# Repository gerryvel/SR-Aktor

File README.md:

# SR Actor

## Description
This repository shows how to switch 3 relais (je 4A max with 2x2A contacts) from Chartplotter with CZone Support and also with the website support.
- Switching Relais Aktor

and send it as NNMEA2000 meassage.
- PGN 127501 // Binary Status Report
- PGN 127502 // Binary Switch Control 
- PGN 126208 // Switch Control for B&G
- PGN 130817 
- PGN 65283
- PGN 65284
- PGN 65288
- PGN 65290 CZone  

In addition, the operation of the relays, data and settings can be accessed via the website.

## Based on the work of

The project requires the NMEA2000 and the NMEA2000_esp32 libraries from Timo Lappalainen: https://github.com/ttlappalainen. 

This project is part of [OpenBoatProject](https://open-boat-projects.org/)

## Wiring diagram

## PCB Layout
PCB by Aisler: [Link](https://aisler.net/p/OFGLZJKF)

## Website

## Chartplotter

I use an B&G Vulcan 7 with Czone Support, after import the file:

Configure Czone file with the CZone Configuration tool V 6.29.22

## Fotos

## Changes

- Version 1.3.2 CZone funtion with B&G Vulcan okay
- Version 1.0 Function with Website control, Monitor on NMEA200 okay (PGN127501)

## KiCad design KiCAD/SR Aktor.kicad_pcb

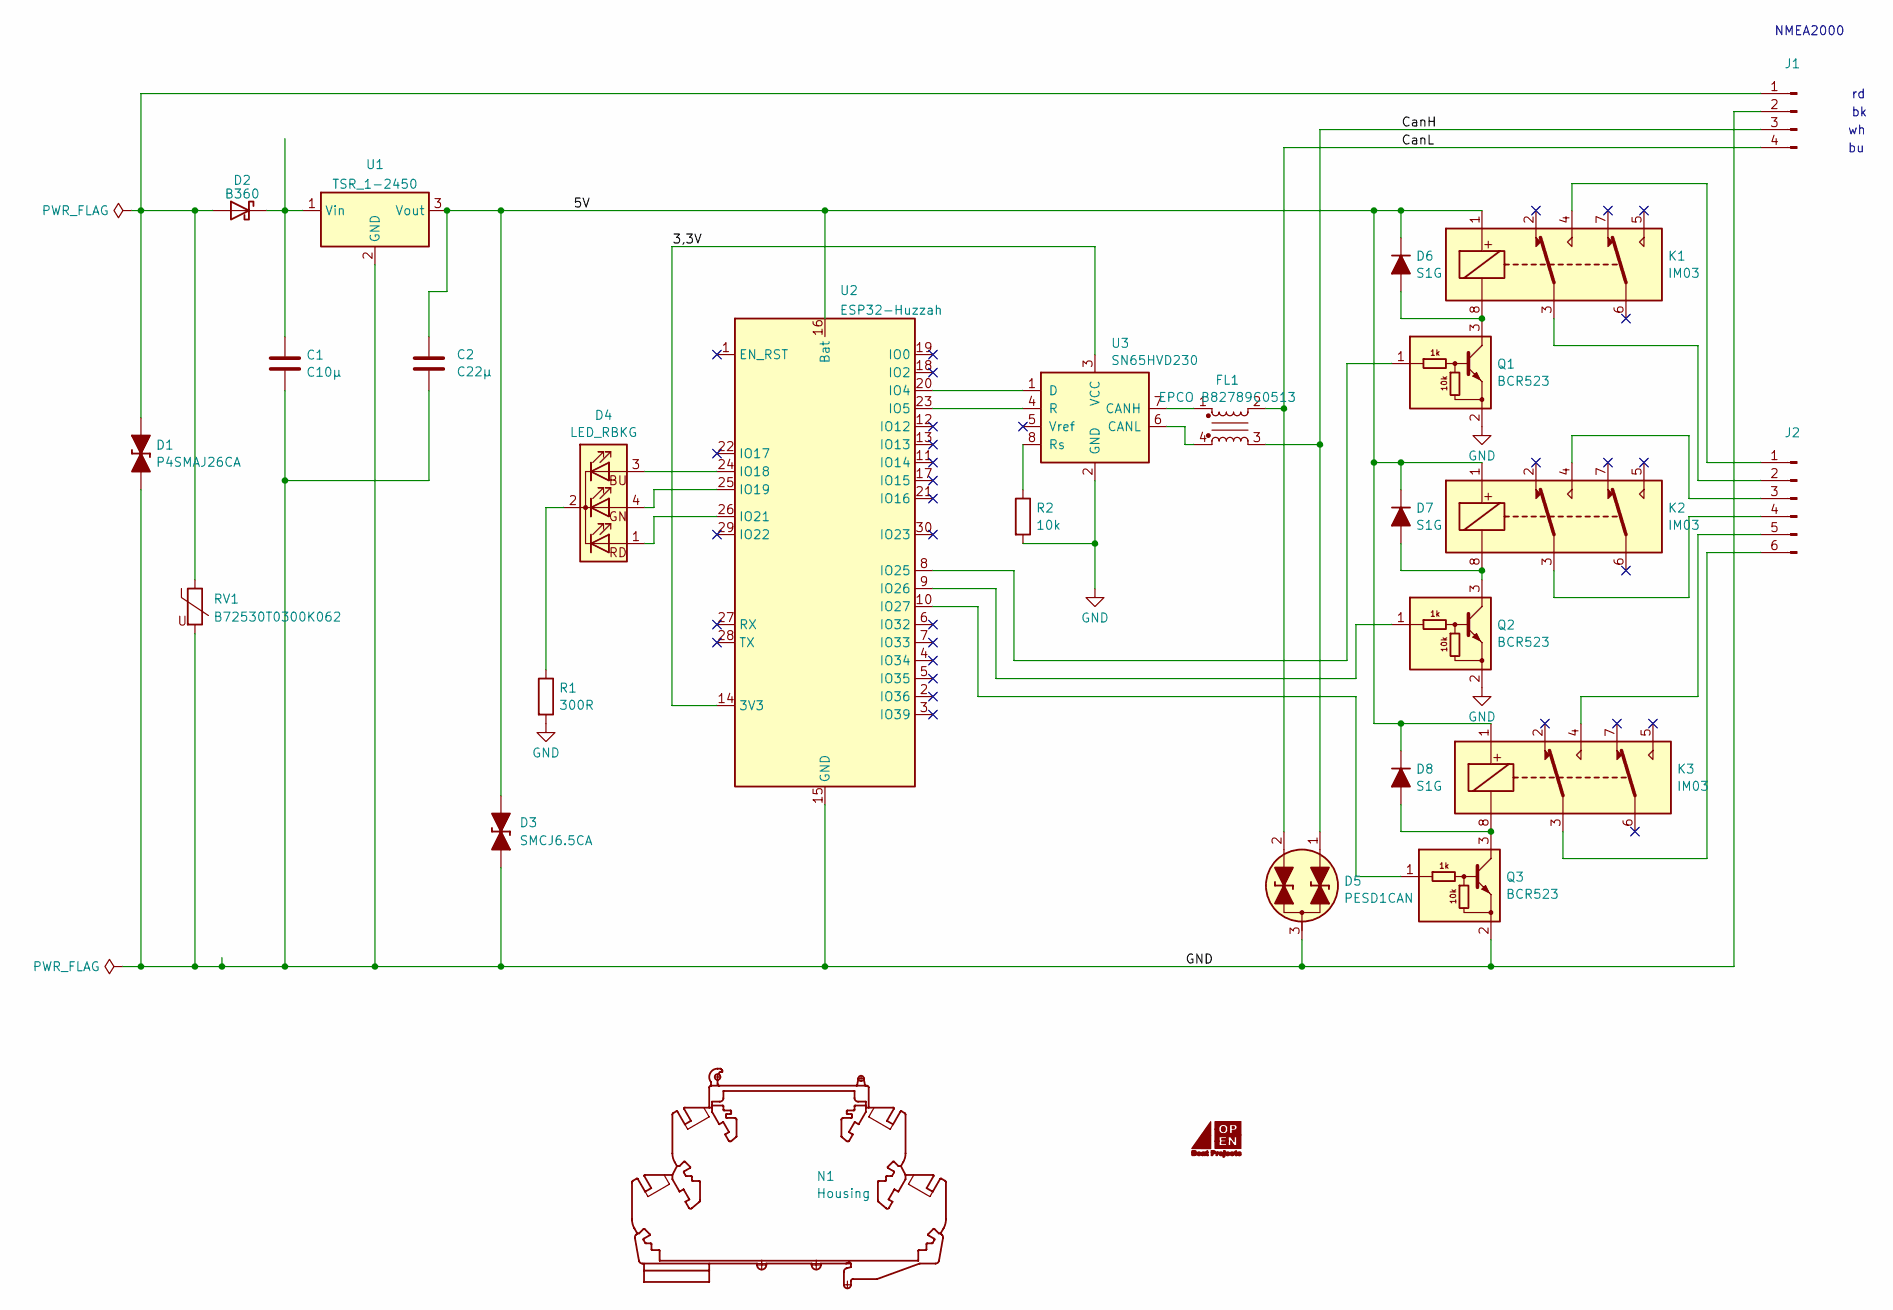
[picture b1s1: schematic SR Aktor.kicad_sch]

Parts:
C1: C10µ; CP_EIA-7343-15_Kemet-W_Pad2.25x2.55mm_HandSolder
C2: C22µ; CP_EIA-7343-15_Kemet-W_Pad2.25x2.55mm_HandSolder
D1: P4SMAJ26CA; D_SMA_TVS
D2: B360; D_SMC
D3: SMCJ6.5CA; D_SMC_TVS
D4: LED_RBKG; PinHeader_1x04_P2.00mm_LED RGB
D5: PESD1CAN; SOT-23
D6, D7, D8: S1G; D_SMA
FL1: EPCO B82789C0513; B82789C0113N002
G1: OpenBoat Logo; Openboatslogo
J1: Conn_01x04_Pin; PinHeader_1x04_P2.54mm_Vertical
J2: Conn_02x03_Pin; PinHeader_2x03_P2.54mm_Vertical
K1, K2, K3: IM03; Relay_DPDT_AXICOM_IMSeries_Pitch5.08mm
N1: Housing; Wago 789-120
Q1, Q2, Q3: BCR523; SOT-23
R1: 300R; R_Axial_DIN0204_L3.6mm_D1.6mm_P7.62mm_Horizontal
R2: 10k; R_Axial_DIN0204_L3.6mm_D1.6mm_P7.62mm_Horizontal
RV1: B72530T0300K062; Fuse_1210_3225Metric_Pad1.42x2.65mm_HandSolder
U1: TSR_1-2450; Converter_DCDC_TRACO_TSR-1_THT
U2: ESP32-Huzzah; Adafruit_ESP32
U3: SN65HVD230; SOIC-8_3.9x4.9mm_P1.27mm

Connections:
/3,3V: U2.14 (3V3), U3.3 (VCC)
/5V: C2.1, D3.1 (K), D6.1 (K), D7.1 (K), D8.1 (K), K1.1, K2.1, K3.1, U1.3 (Vout), U2.16 (Bat)
/CanH: D5.1 (A1), FL1.3, J1.3
/CanL: D5.2 (A2), FL1.2, J1.4
GND: C1.2, C2.2, D1.1 (K), D3.2 (A), D5.3 (Com), J1.2, Q1.2 (E), Q2.2 (E), Q3.2 (E), R1.2, R2.2, RV1.2, U1.2 (GND), U2.15 (GND), U3.2 (GND)
unnamed: D1.2 (A), D2.2 (A), J1.1, RV1.1
unnamed: C1.1, D2.1 (K), U1.1 (Vin)
unnamed: D4.1 (BA), U2.26 (IO21)
unnamed: D4.4 (GA), U2.25 (IO19)
unnamed: D4.2 (K), R1.1
unnamed: D4.3 (R), U2.24 (IO18)
unnamed: D6.2 (A), K1.8, Q1.3 (C)
unnamed: D7.2 (A), K2.8, Q2.3 (C)
unnamed: D8.2 (A), K3.8, Q3.3 (C)
unnamed: J2.1, K1.4
unnamed: J2.2, K1.3
unnamed: J2.3, K2.4
unnamed: J2.4, K2.3
unnamed: J2.5, K3.4
unnamed: J2.6, K3.3
unnamed: Q1.1 (B), U2.8 (IO25)
unnamed: Q2.1 (B), U2.9 (IO26)
unnamed: Q3.1 (B), U2.10 (IO27)
unnamed: U2.20 (IO4), U3.1 (D)
unnamed: U2.23 (IO5), U3.4 (R)
unnamed: FL1.1, U3.7 (CANH)
unnamed: FL1.4, U3.6 (CANL)
unnamed: R2.1, U3.8 (Rs)

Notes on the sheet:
NMEA2000

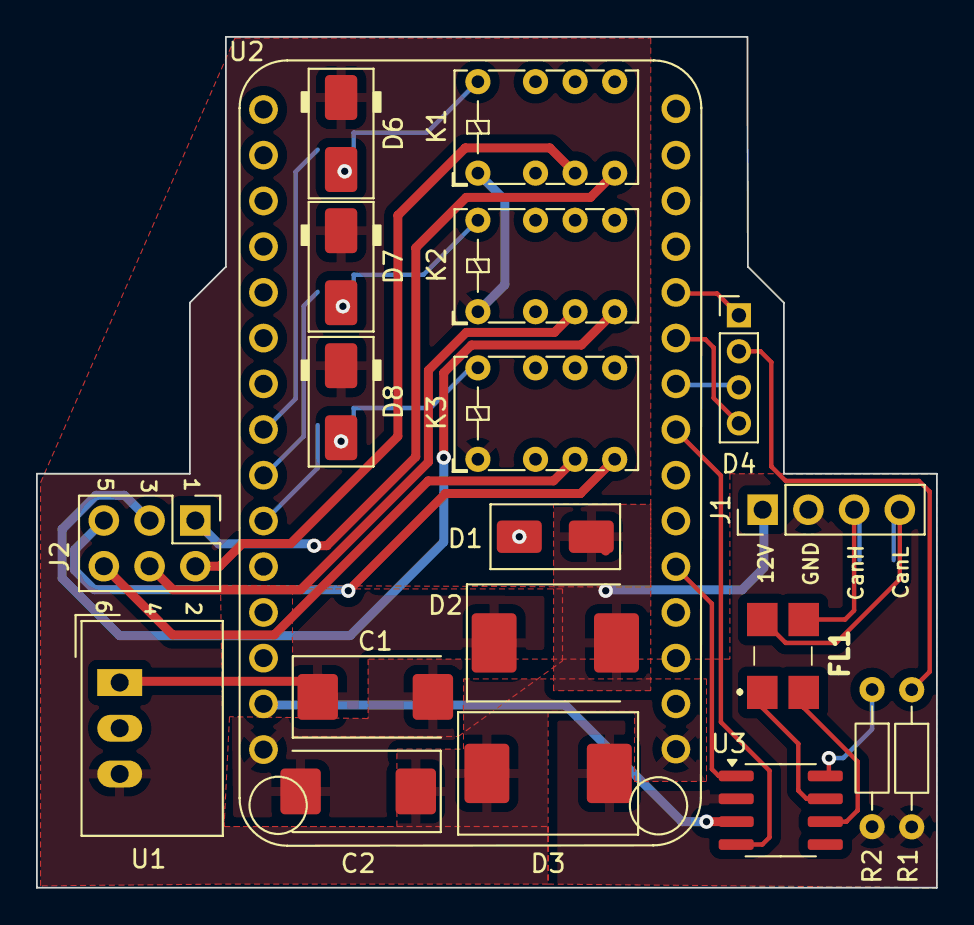
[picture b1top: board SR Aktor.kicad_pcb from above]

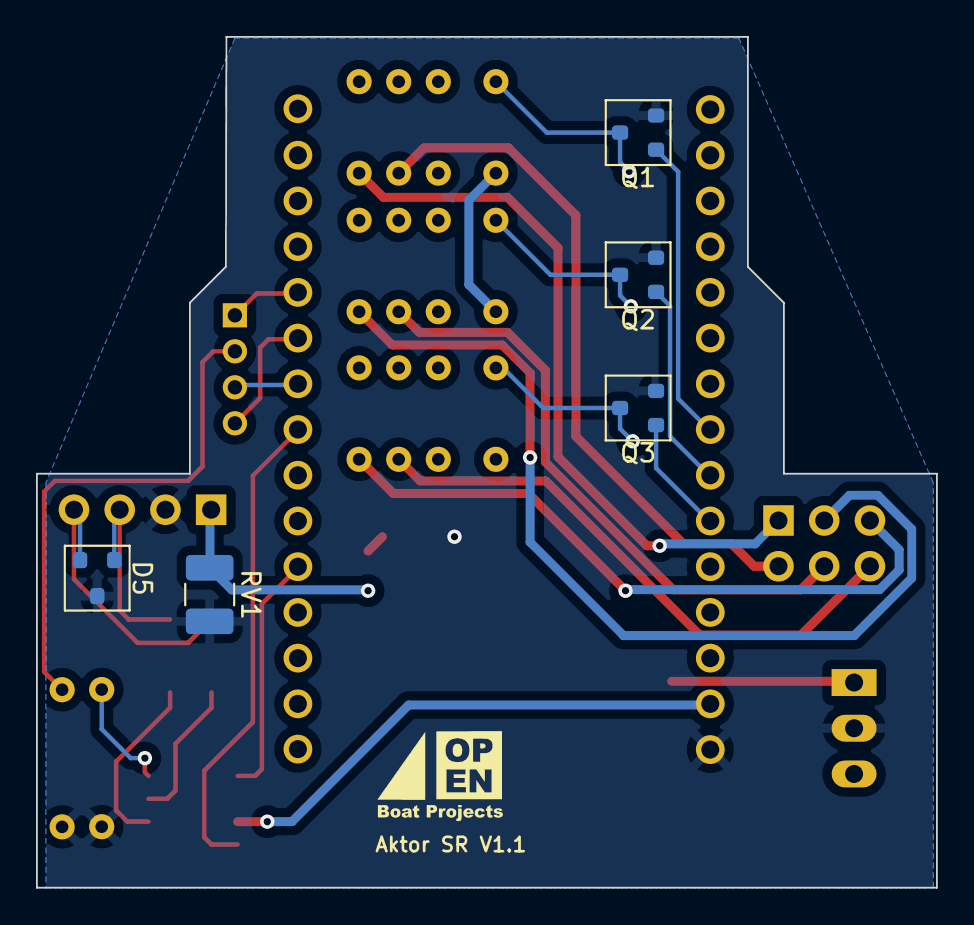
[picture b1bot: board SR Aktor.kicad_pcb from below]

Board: 2 copper layers, 50.0 x 47.3 mm, 26 parts (6 on the bottom side), 28 nets.

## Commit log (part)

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2025-04-06 V 0.9
2025-04-06 create
2025-05-20 Update extensionsFile
2025-06-18 V 1.0
2025-08-30 Kicad added
2025-10-08 V 1.0.1
2025-10-21 Replace wiring diagram image in README
    Updated wiring diagram image in README.
2025-10-21 Add additional images to README
2025-10-21 V 1.1
2026-06-18 V 1.2
2026-06-24 V 2.6
2026-06-25 V 1.3
2026-06-26 V 1.3 CZone Schalten&Status okay, Geräteansicht 3 Relais okay
2026-06-26 V 1.3.1
2026-06-26 V1.3.1 stable Czone/N2k N2K behavior (switching+status+device list)
2026-06-26 V 1.3.2 cleaning
2026-06-26 V 1.3.2
2026-06-27 Status toggle failure
